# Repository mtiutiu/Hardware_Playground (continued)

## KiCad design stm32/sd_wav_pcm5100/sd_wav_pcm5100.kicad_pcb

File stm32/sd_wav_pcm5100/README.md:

#### SD Card Wav player using STM32 with PCM5102 audio DAC

The project uses also Petit FAT File System Module - ELM by ChaN (http://elm-chan.org/fsw/ff/00index_p.html).

##### 3D renderings of pcb

Top view | Bottom view
------------ | -------------
 | 

The only thing I ask if using this project is to at least mention my name and if I don't ask too much you can also support my effort using the below button. Thanks.

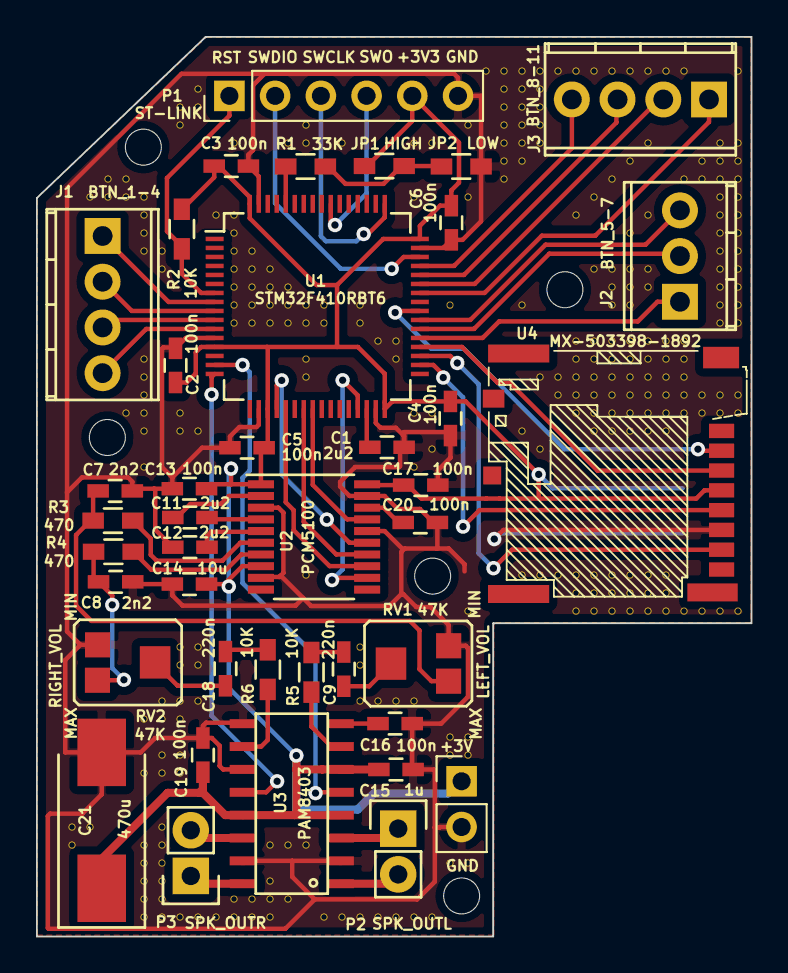
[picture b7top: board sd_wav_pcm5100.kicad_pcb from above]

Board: 2 copper layers, 39.7 x 50.0 mm, 323 parts (1 on the bottom side), 50 nets.

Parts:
C1, C11, C14: 2u2; C_0603_HandSoldering
C2, C3, C4, C5, C6, C13, C16, C17, C19, C20: 100n; C_0603_HandSoldering
C7, C8: 2n2; C_0603_HandSoldering
C9, C18: 220n; C_0603_HandSoldering
C10: 47u; C_0805_HandSoldering
C12: 10u; C_0603_HandSoldering
C15: 1u; C_0603_HandSoldering
C21: 470u; Tantalum_Case-D_EIA-7343-31_Hand
J1: BTN_1-4; TerminalBlock_Pheonix_MPT-2.54mm_4pol
J2: BTN_5-7; TerminalBlock_Pheonix_MPT-2.54mm_3pol
J3: BTN_8-11; TerminalBlock_Pheonix_MPT-2.54mm_4pol
JP1: HIGH; R_0603_HandSoldering
JP2: LOW; R_0603_HandSoldering
P1: ST-LINK; Pin_Header_Straight_1x06_Pitch2.54mm
P2: SPK_OUTL; Pin_Header_Straight_1x02
P3: SPK_OUTR; Pin_Header_Straight_1x02
P4: Supply; Pin_Header_Straight_1x02_Pitch2.54mm
R1: 33K; R_0603_HandSoldering
R2, R5, R6: 10K; R_0603_HandSoldering
R3, R4: 470; R_0603_HandSoldering
RV1, RV2: 47K; TC-33X-2
U1: STM32F410RBT6; LQFP-64_10x10mm_Pitch0.5mm
U2: PCM5100; TSSOP-20_4.4x6.5mm_Pitch0.65mm
U3: PAM8403; SOP16L
U4: MX-503398-1892
V2_44, V2_45, V3_9, V3_44, V4_8, V4_9, V5_8, V5_9, V5_21, V6_9, V6_10, V6_11, V6_12, V6_18, V6_19, V6_20, V6_21, V6_22, V6_24, V6_38, V6_41, V6_45, V6_46, V6_47, V6_48, V6_49, V7_12, V7_13, V7_37, V7_38, V7_40, V7_41, V7_44, V7_45, V7_46, V7_47, V7_48, V7_49, V8_4, V8_5, V8_21, V8_22, V8_34, V8_35, V8_37, V8_38, V8_40, V8_41, V8_49, V9_3, V9_4, V9_22, V9_34, V9_35, V9_37, V9_49, V10_10, V10_49, V11_6, V11_10, V11_11, V11_12, V11_13, V11_14, V11_15, V11_16, V11_48, V11_49, V12_12, V12_13, V12_14, V12_15, V12_16, V12_48, V12_49, V13_13, V13_14, V13_15, V13_16, V13_45, V13_47, V13_48, V13_49, V14_6, V14_14, V14_15, V14_16, V14_45, V14_48, V15_5, V15_6, V15_15, V15_16, V15_18, V15_19, V15_30, V15_45, V16_15, V16_16, V16_49, V17_6, V17_49, V18_15, V18_16, V18_34, V18_35, V18_37, V18_49, V19_17, V19_37, V19_49, V20_17, V20_18, V20_37, V20_49, V21_6, V21_9, V21_21, V21_24, V21_37, V21_49, V22_6, V22_21, V22_23, V22_49, V23_15, V23_39, V23_40, V23_46, V24_5, V24_9, V24_32, V24_39, V24_40, V24_46, V25_2, V26_2, V26_3, V26_4, V26_5, V26_6, V26_7, V26_8, V27_2, V27_3, V27_4, V27_5, V27_6, V27_7, V27_15, V27_22, V27_30, V28_2, V28_3, V28_4, V28_5, V28_6, V28_19, V28_23, V28_30, V29_2, V29_19, V29_20, V29_30, V30_2, V30_10, V30_17, V30_18, V30_19, V30_20, V30_21, V30_30, V30_31, V30_32, V31_2, V31_9, V31_13, V31_17, V31_18, V31_19, V31_20, V31_21, V31_22, V31_30, V31_31, V31_32, V32_2, V32_8, V32_13, V32_14, V32_15, V32_17, V32_18, V32_19, V32_20, V32_21, V32_22, V32_30, V32_31, V32_32, V33_2, V33_7, V33_11, V33_13, V33_14, V33_15, V33_17, V33_18, V33_19, V33_20, V33_21, V33_22, V33_30, V33_31, V33_32, V34_2, V34_6, V34_10, V34_13, V34_14, V34_17, V34_18, V34_19, V34_20, V34_21, V34_22, V34_30, V34_31, V34_32, V35_2, V35_17, V35_18, V35_19, V35_20, V35_21, V35_22, V35_30, V35_31, V35_32, V36_2, V36_8, V36_17, V36_18, V36_19, V36_20, V36_21, V36_32, V37_7, V37_8, V37_20, V37_21, V37_32, V38_6, V38_7, V38_8, V38_9, V38_10, V38_11, V38_12, V38_13, V38_14, V38_15, V38_16, V38_20, V38_21, V38_32, V39_2, V39_6, V39_7, V39_8, V39_9, V39_10, V39_11, V39_12, V39_13, V39_14, V39_15, V39_16, V39_20, V39_21, V39_32: AUTO_VIA; VIA_MATRIX

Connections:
+3V3: C2.1, C3.1, C4.1, C5.1, C6.1, C10.1, C12.2, C13.1, C15.2, C17.1, C19.1, C21.1, JP1.2, P1.5, P4.1, R2.2, U1.13, U1.19, U1.32, U1.48, U1.64, U2.1, U2.8, U2.20, U3.4, U3.6, U3.13, U4.4
/BTN1: J1.1, U1.8
/BTN2: J1.2, U1.9
/BTN3: J1.3, U1.10
/BTN4: J1.4, U1.11
/BTN5: J2.1, U1.37
/BTN6: J2.2, U1.38
/BTN7: J2.3, U1.39
/BTN8: J3.1, U1.42
/BTN9: J3.2, U1.43
/BTN10: J3.3, U1.44
/BTN11: J3.4, U1.45
/I2S_BCLK: U1.21, U2.13
/I2S_DATA: U1.23, U2.14
/I2S_LRCLK: U1.20, U2.15
/I2S_MCLK: U1.29, U2.12
/PAM8403_MUTE: U1.15, U3.5
/PAM8403_STANDBY: U1.16, U3.12
/PCM5100_MUTE: U1.24, U2.17
/PCM5100_OUTL: C7.2, R3.2, RV1.1
/PCM5100_OUTR: C8.2, R4.2, RV2.3
/SD_CS: U1.40, U4.2
/SD_DI: U1.36, U4.3
/SD_DO: U1.35, U4.7
/SD_SCLK: U1.34, U4.5
/SWCLK: P1.3, U1.49
/SWDIO: P1.2, U1.46
/SWO: P1.4, U1.55
/nRST: P1.1, R2.1, U1.7
GND: C1.2, C2.2, C3.2, C4.2, C5.2, C6.2, C7.1, C8.1, C10.2, C12.1, C13.2, C14.2, C15.1, C16.1, C17.2, C19.2, C20.2, C21.2, JP2.1, P1.6, P4.2, RV1.3, RV2.1, U1.12, U1.18, U1.31, U1.47, U1.63, U2.3, U2.9, U2.16, U2.19, U3.2, U3.9, U3.11, U3.15, U4.6, V2_44.1, V2_45.1, V3_9.1, V3_44.1, V4_8.1, V4_9.1, V5_8.1, V5_9.1, V5_21.1, V6_9.1, V6_10.1, V6_11.1, V6_12.1, V6_18.1, V6_19.1, V6_20.1, V6_21.1, V6_22.1, V6_24.1, V6_38.1, V6_41.1, V6_45.1, V6_46.1, V6_47.1, V6_48.1, V6_49.1, V7_12.1, V7_13.1, V7_37.1, V7_38.1, V7_40.1, V7_41.1, V7_44.1, V7_45.1, V7_46.1, V7_47.1, V7_48.1, V7_49.1, V8_4.1, V8_5.1, V8_21.1, V8_22.1, V8_34.1, V8_35.1, V8_37.1, V8_38.1, V8_40.1, V8_41.1, V8_49.1, V9_3.1, V9_4.1, V9_22.1, V9_34.1, V9_35.1, V9_37.1, V9_49.1, V10_10.1, V10_49.1, V11_6.1, V11_10.1, V11_11.1, V11_12.1, V11_13.1, V11_14.1, V11_15.1, V11_16.1, V11_48.1, V11_49.1, V12_12.1, V12_13.1, V12_14.1, V12_15.1, V12_16.1, V12_48.1, V12_49.1, V13_13.1, V13_14.1, V13_15.1, V13_16.1, V13_45.1, V13_47.1, V13_48.1, V13_49.1, V14_6.1, V14_14.1, V14_15.1, V14_16.1, V14_45.1, V14_48.1, V15_5.1, V15_6.1, V15_15.1, V15_16.1, V15_18.1, V15_19.1, V15_30.1, V15_45.1, V16_15.1, V16_16.1, V16_49.1, V17_6.1, V17_49.1, V18_15.1, V18_16.1, V18_34.1, V18_35.1, V18_37.1, V18_49.1, V19_17.1, V19_37.1, V19_49.1, V20_17.1, V20_18.1, V20_37.1, V20_49.1, V21_6.1, V21_9.1, V21_21.1, V21_24.1, V21_37.1, V21_49.1, V22_6.1, V22_21.1, V22_23.1, V22_49.1, V23_15.1, V23_39.1, V23_40.1, V23_46.1, V24_5.1, V24_9.1, V24_32.1, V24_39.1, V24_40.1, V24_46.1, V25_2.1, V26_2.1, V26_3.1, V26_4.1, V26_5.1, V26_6.1, V26_7.1, V26_8.1, V27_2.1, V27_3.1, V27_4.1, V27_5.1, V27_6.1, V27_7.1, V27_15.1, V27_22.1, V27_30.1, V28_2.1, V28_3.1, V28_4.1, V28_5.1, V28_6.1, V28_19.1, V28_23.1, V28_30.1, V29_2.1, V29_19.1, V29_20.1, V29_30.1, V30_2.1, V30_10.1, V30_17.1, V30_18.1, V30_19.1, V30_20.1, V30_21.1, V30_30.1, V30_31.1, V30_32.1, V31_2.1, V31_9.1, V31_13.1, V31_17.1, V31_18.1, V31_19.1, V31_20.1, V31_21.1, V31_22.1, V31_30.1, V31_31.1, V31_32.1, V32_2.1, V32_8.1, V32_13.1, V32_14.1, V32_15.1, V32_17.1, V32_18.1, V32_19.1, V32_20.1, V32_21.1, V32_22.1, V32_30.1, V32_31.1, V32_32.1, V33_2.1, V33_7.1, V33_11.1, V33_13.1, V33_14.1, V33_15.1, V33_17.1, V33_18.1, V33_19.1, V33_20.1, V33_21.1, V33_22.1, V33_30.1, V33_31.1, V33_32.1, V34_2.1, V34_6.1, V34_10.1, V34_13.1, V34_14.1, V34_17.1, V34_18.1, V34_19.1, V34_20.1, V34_21.1, V34_22.1, V34_30.1, V34_31.1, V34_32.1, V35_2.1, V35_17.1, V35_18.1, V35_19.1, V35_20.1, V35_21.1, V35_22.1, V35_30.1, V35_31.1, V35_32.1, V36_2.1, V36_8.1, V36_17.1, V36_18.1, V36_19.1, V36_20.1, V36_21.1, V36_32.1, V37_7.1, V37_8.1, V37_20.1, V37_21.1, V37_32.1, V38_6.1, V38_7.1, V38_8.1, V38_9.1, V38_10.1, V38_11.1, V38_12.1, V38_13.1, V38_14.1, V38_15.1, V38_16.1, V38_20.1, V38_21.1, V38_32.1, V39_2.1, V39_6.1, V39_7.1, V39_8.1, V39_9.1, V39_10.1, V39_11.1, V39_12.1, V39_13.1, V39_14.1, V39_15.1, V39_16.1, V39_20.1, V39_21.1, V39_32.1
unnamed: C1.1, U1.30
unnamed: C9.1, R5.2
unnamed: C9.2, RV1.2
unnamed: C11.1, U2.4
unnamed: C11.2, U2.2
unnamed: C14.1, U2.5
unnamed: C16.2, U3.8
unnamed: C18.1, RV2.2
unnamed: C18.2, R6.1
unnamed: C20.1, U2.18
unnamed: JP1.1, JP2.2, R1.2
unnamed: P2.1, U3.3
unnamed: P2.2, U3.1
unnamed: P3.1, U3.16
unnamed: P3.2, U3.14
unnamed: R1.1, U1.60
unnamed: R3.1, U2.6
unnamed: R4.1, U2.7
unnamed: R5.1, U3.7
unnamed: R6.2, U3.10
